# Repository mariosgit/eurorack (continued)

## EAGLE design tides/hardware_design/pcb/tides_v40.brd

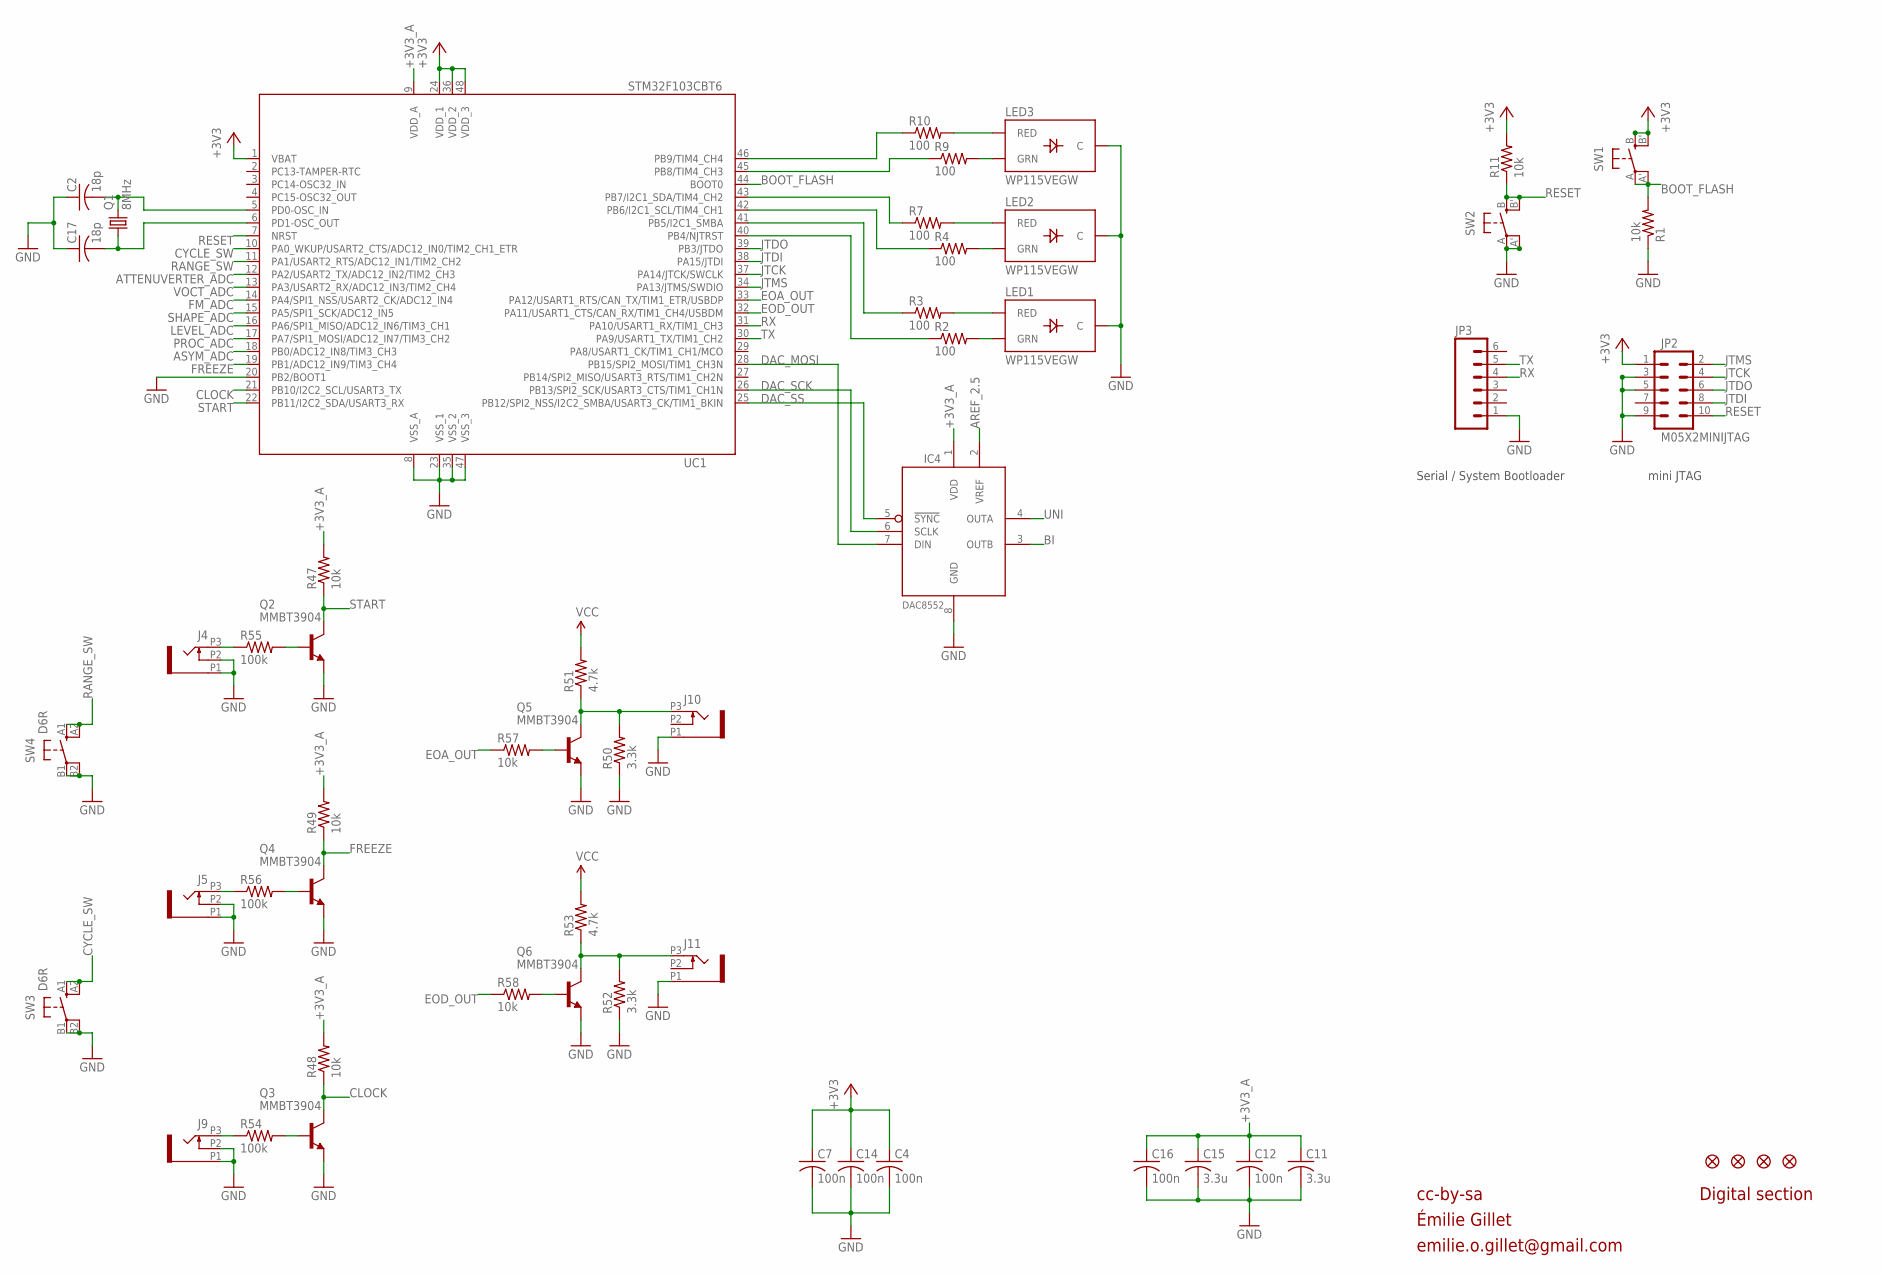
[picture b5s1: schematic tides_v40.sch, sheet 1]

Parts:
C2, C17: 18p; C0603
C4, C7, C12, C14, C16: 100n; C0603
C11, C15: 3.3u; C0603
IC4: DAC8552; MSOP-8
J4, J5, J9, J10, J11: PJ301_THONKICONN6; WQP_PJ_301M6
JP2: M05X2MINIJTAG; 2X5-1.27
JP3: M06SIP; 1X06
JP4, JP5, JP6, JP7: FIDUCIAL1X2; FIDUCIAL-1X2
LED1, LED2, LED3: WP115VEGW; LED-BICOLOR-THROUGHHOLE
Q1: 8MHz; HC49UP
Q2, Q3, Q4, Q5, Q6: MMBT3904; SOT23-BEC
R1, R11, R47, R48, R49, R57, R58: 10k; R0603
R2, R3, R4, R7, R9, R10: 100; R0603
R50, R52: 3.3k; R0603
R51, R53: 4.7k; R0603
R54, R55, R56: 100k; R0603
SW1, SW2: EVQQ2; EVQ-Q2
SW3, SW4: D6R
UC1: STM32F103CBT6; LQFP48

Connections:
+3V3: C4.1, C7.1, C14.1, JP2.1, R11.2, SW1.B (S), SW1.B' (S1), UC1.1 (VBAT), UC1.24 (VDD_1), UC1.36 (VDD_2), UC1.48 (VDD_3); also elsewhere on the board
+3V3_A: C11.1, C12.1, C15.1, C16.1, IC4.1 (VDD), R47.2, R48.2, R49.2, UC1.9 (VDD_A); also elsewhere on the board
AREF_2.5: IC4.2 (VREF); also elsewhere on the board
ASYM_ADC: UC1.18 (PB0/ADC12_IN8/TIM3_CH3); also elsewhere on the board
ATTENUVERTER_ADC: UC1.12 (PA2/USART2_TX/ADC12_IN2/TIM2_CH3); also elsewhere on the board
BI: IC4.3 (OUTB); also elsewhere on the board
BOOT_FLASH: R1.2, SW1.A, SW1.A' (P1), UC1.44 (BOOT0)
CLOCK: Q3.C, R48.1, UC1.21 (PB10/I2C2_SCL/USART3_TX)
CYCLE_SW: SW3.A1 (S), SW3.A2 (S1), UC1.10 (PA0_WKUP/USART2_CTS/ADC12_IN0/TIM2_CH1_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)
DAC_MOSI: IC4.7 (DIN), UC1.28 (PB15/SPI2_MOSI/TIM1_CH3N)
DAC_SCK: IC4.6 (SCLK), UC1.26 (PB13/SPI2_SCK/USART3_CTS/TIM1_CH1N)
DAC_SS: IC4.5 (!SYNC), UC1.25 (PB12/SPI2_NSS/I2C2_SMBA/USART3_CK/TIM1_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)
EOA_OUT: R57.1, UC1.33 (PA12/USART1_RTS/CAN_TX/TIM1_ETR/USBDP)
EOD_OUT: R58.1, UC1.32 (PA11/USART1_CTS/CAN_RX/TIM1_CH4/USBDM)
FM_ADC: UC1.14 (PA4/SPI1_NSS/USART2_CK/ADC12_IN4); also elsewhere on the board
FREEZE: Q4.C, R49.1, UC1.19 (PB1/ADC12_IN9/TIM3_CH4)
GND: C2.1, C4.2, C7.2, C11.2, C12.2, C14.2, C15.2, C16.2, C17.1, IC4.8 (GND), J4.P1 (1), J4.P2 (2), J5.P1 (1), J5.P2 (2), J9.P1 (1), J9.P2 (2), J10.P1 (1), J11.P1 (1), JP2.3, JP2.5, JP2.9, JP3.1, LED1.2 (C), LED2.2 (C), LED3.2 (C), Q2.E, Q3.E, Q4.E, Q5.E, Q6.E, R1.1, R50.1, R52.1, SW2.A, SW2.A' (P1), SW3.B1, SW3.B2 (P1), SW4.B1, SW4.B2 (P1), UC1.8 (VSS_A), UC1.20 (PB2/BOOT1), UC1.23 (VSS_1), UC1.35 (VSS_2), UC1.47 (VSS_3); also elsewhere on the board
JTCK: JP2.4, UC1.37 (PA14/JTCK/SWCLK)
JTDI: JP2.8, UC1.38 (PA15/JTDI)
JTDO: JP2.6, UC1.39 (PB3/JTDO)
JTMS: JP2.2, UC1.34 (PA13/JTMS/SWDIO)
LEVEL_ADC: UC1.16 (PA6/SPI1_MISO/ADC12_IN6/TIM3_CH1); also elsewhere on the board
unnamed: C2.2, Q1.2, UC1.5 (PD0-OSC_IN)
unnamed: C17.2, Q1.1, UC1.6 (PD1-OSC_OUT)
unnamed: J5.P3 (3), R56.1
unnamed: Q4.B, R56.2
unnamed: J9.P3 (3), R54.1
unnamed: Q3.B, R54.2
unnamed: Q6.B, R58.2
unnamed: J11.P3 (3), Q6.C, R52.2, R53.1
unnamed: LED3.3 (RED), R10.2
unnamed: LED3.1 (GRN), R9.2
unnamed: LED2.3 (RED), R7.2
unnamed: LED2.1 (GRN), R4.2
unnamed: LED1.3 (RED), R3.2
unnamed: LED1.1 (GRN), R2.2
unnamed: R10.1, UC1.46 (PB9/TIM4_CH4)
unnamed: R9.1, UC1.45 (PB8/TIM4_CH3)
unnamed: R7.1, UC1.43 (PB7/I2C1_SDA/TIM4_CH2)
unnamed: R4.1, UC1.42 (PB6/I2C1_SCL/TIM4_CH1)
unnamed: R3.1, UC1.41 (PB5/I2C1_SMBA)
unnamed: R2.1, UC1.40 (PB4/NJTRST)
unnamed: J10.P3 (3), Q5.C, R50.2, R51.1
unnamed: Q5.B, R57.2
unnamed: J4.P3 (3), R55.1
unnamed: Q2.B, R55.2
PROC_ADC: UC1.17 (PA7/SPI1_MOSI/ADC12_IN7/TIM3_CH2); also elsewhere on the board
RANGE_SW: SW4.A1 (S), SW4.A2 (S1), UC1.11 (PA1/USART2_RTS/ADC12_IN1/TIM2_CH2)
RESET: JP2.10, R11.1, SW2.B (S), SW2.B' (S1), UC1.7 (NRST)
RX: JP3.4, UC1.31 (PA10/USART1_RX/TIM1_CH3)
SHAPE_ADC: UC1.15 (PA5/SPI1_SCK/ADC12_IN5); also elsewhere on the board
START: Q2.C, R47.1, UC1.22 (PB11/I2C2_SDA/USART3_RX)
TX: JP3.5, UC1.30 (PA9/USART1_TX/TIM1_CH2)
UNI: IC4.4 (OUTA); also elsewhere on the board
VCC: R51.2, R53.2; also elsewhere on the board
VOCT_ADC: UC1.13 (PA3/USART2_RX/ADC12_IN3/TIM2_CH4); also elsewhere on the board

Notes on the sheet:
cc-by-sa
Digital section
Serial / System Bootloader
mini JTAG
Émilie Gillet
emilie.o.gillet@gmail.com

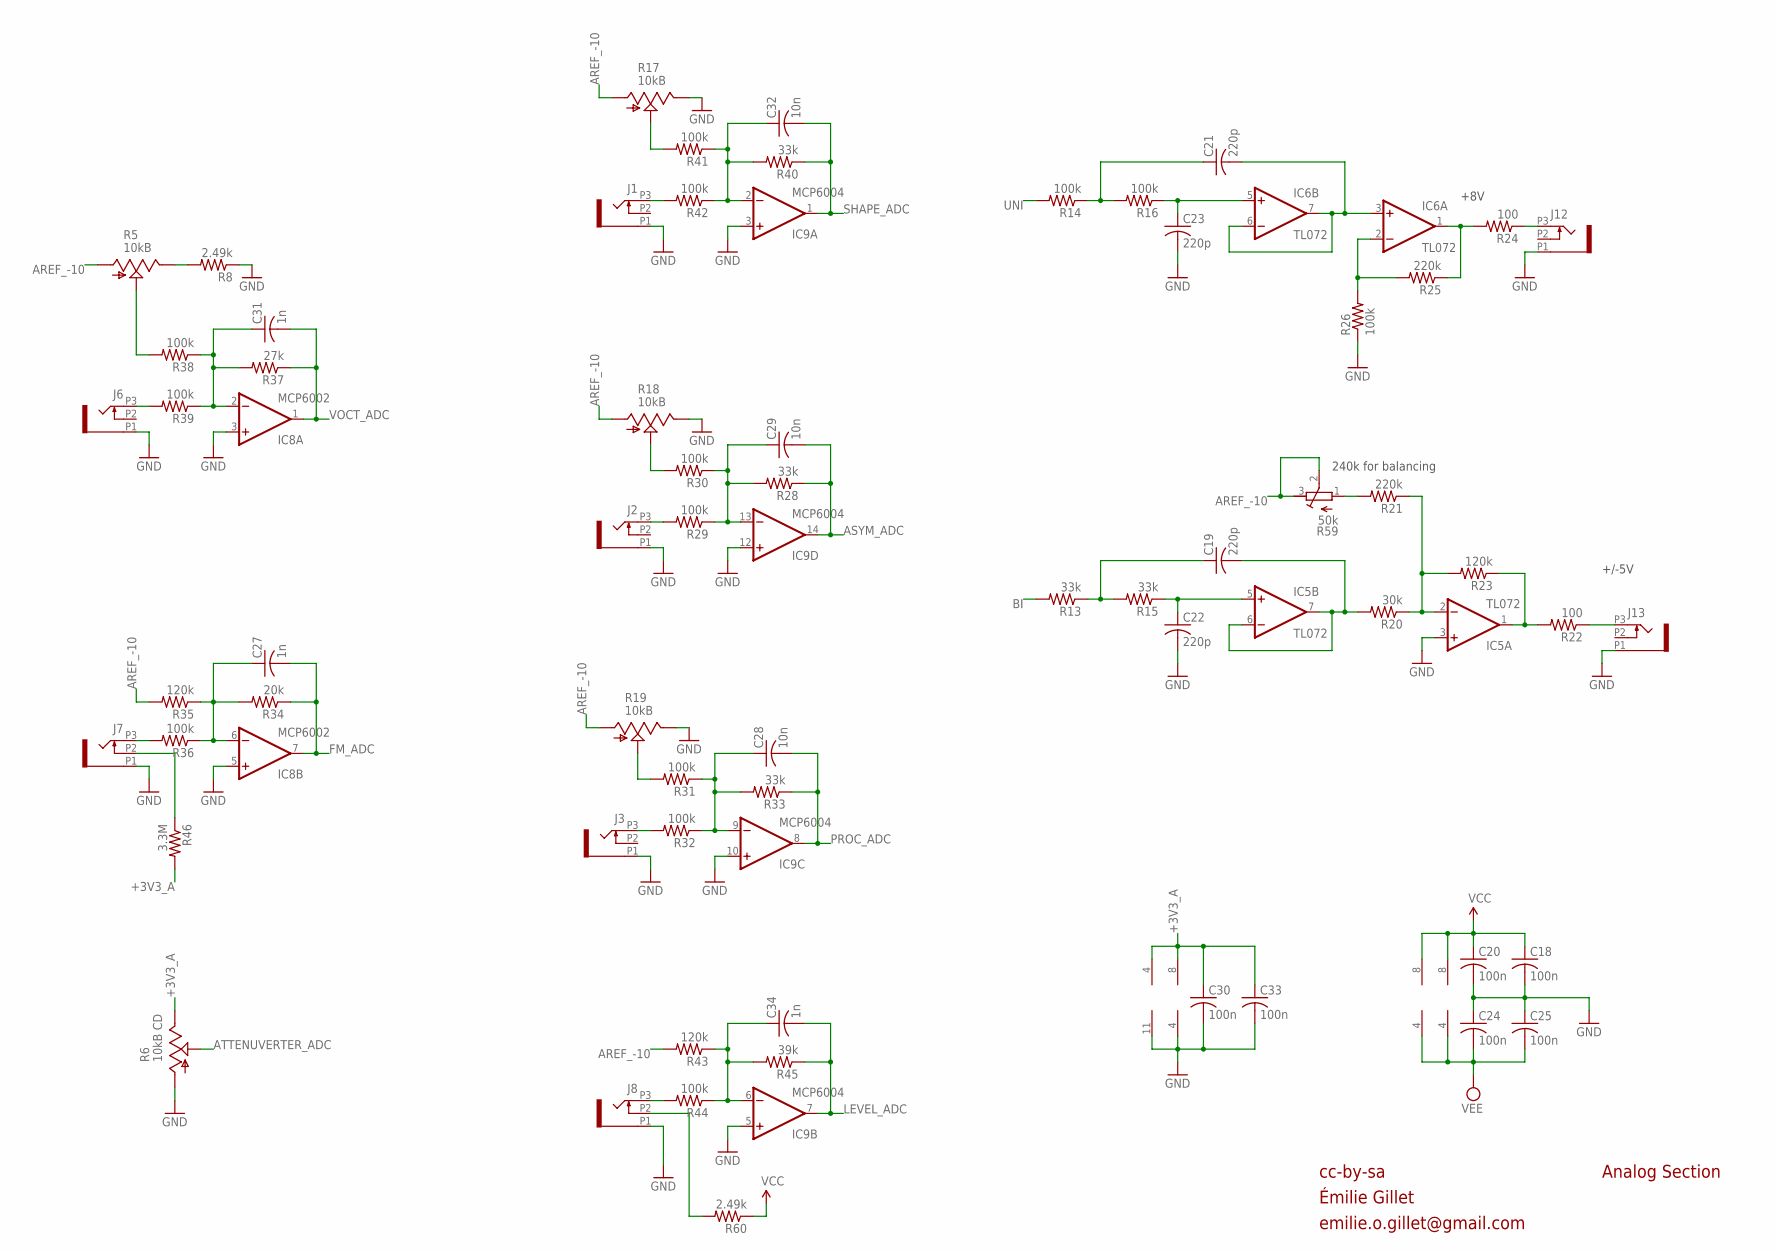
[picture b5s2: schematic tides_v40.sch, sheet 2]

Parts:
C18, C20, C24, C25, C30, C33: 100n; C0603
C19, C21, C22, C23: 220p; C0603
C27, C31, C34: 1n; C0603
C28, C29, C32: 10n; C0603
IC5, IC6: TL072; SO08
IC8: MCP6002; SO08
IC9: MCP6004; SO14
J1, J2, J3, J6, J7, J8, J12, J13: PJ301_THONKICONN6; WQP_PJ_301M6
R5, R17, R18, R19: 10kB; ALPS_POT_VERTICAL_PS
R6: 10kB CD; ALPS_POT_VERTICAL_PS
R8: 2.49k; R0603
R13, R15, R28, R33, R40: 33k; R0603
R14, R16, R26, R29, R30, R31, R32, R36, R38, R39, R41, R42, R44: 100k; R0603
R20: 30k; R0603
R21, R25: 220k; R0603
R22, R24: 100; R0603
R23, R35, R43: 120k; R0603
R34: 20k; R0603
R37: 27k; R0603
R45: 39k; R0603
R46: 3.3M; R0603
R59: 50k; RTRIM3296X
R60: 2.49k; R0805

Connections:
+3V3_A: C30.1, C33.1, IC8.8 (V+), IC9.4 (V+), R6.P$1 (E), R46.2; also elsewhere on the board
AREF_-10: R5.P$3 (A), R17.P$3 (A), R18.P$3 (A), R19.P$3 (A), R35.2, R43.2, R59.2 (S), R59.3 (A); also elsewhere on the board
ASYM_ADC: C29.2, IC9.14 (OUT), R28.1; also elsewhere on the board
ATTENUVERTER_ADC: R6.P$2 (S); also elsewhere on the board
BI: R13.2; also elsewhere on the board
BI_OUT: IC5.1 (OUT), R22.2, R23.1
FM_ADC: C27.2, IC8.7 (OUT), R34.1; also elsewhere on the board
F_CV: IC5.2 (-IN), R20.1, R21.1, R23.2
GND: C18.2, C20.2, C22.2, C23.2, C24.1, C25.1, C30.2, C33.2, IC5.3 (+IN), IC8.3 (+IN), IC8.4 (V-), IC8.5 (+IN), IC9.3 (+IN), IC9.5 (+IN), IC9.10 (+IN), IC9.11 (V-), IC9.12 (+IN), J1.P1 (1), J2.P1 (1), J3.P1 (1), J6.P1 (1), J7.P1 (1), J8.P1 (1), J12.P1 (1), J13.P1 (1), R6.P$3 (A), R8.1, R17.P$1 (E), R18.P$1 (E), R19.P$1 (E), R26.1; also elsewhere on the board
LEVEL_ADC: C34.2, IC9.7 (OUT), R45.1; also elsewhere on the board
unnamed: J1.P3 (3), R42.2
unnamed: C32.1, IC9.2 (-IN), R40.2, R41.1, R42.1
unnamed: R17.P$2 (S), R41.2
unnamed: J2.P3 (3), R29.2
unnamed: C29.1, IC9.13 (-IN), R28.2, R29.1, R30.1
unnamed: J7.P2 (2), R46.1
unnamed: R18.P$2 (S), R30.2
unnamed: J3.P3 (3), R32.2
unnamed: C28.1, IC9.9 (-IN), R31.1, R32.1, R33.2
unnamed: R19.P$2 (S), R31.2
unnamed: J8.P3 (3), R44.2
unnamed: C34.1, IC9.6 (-IN), R43.1, R44.1, R45.2
unnamed: J6.P3 (3), R39.2
unnamed: C31.1, IC8.2 (-IN), R37.2, R38.1, R39.1
unnamed: R5.P$2 (S), R38.2
unnamed: J13.P3 (3), R22.1
unnamed: R5.P$1 (E), R8.2
unnamed: J7.P3 (3), R36.2
unnamed: C27.1, IC8.6 (-IN), R34.2, R35.1, R36.1
unnamed: R21.2, R59.1 (E)
unnamed: IC6.2 (-IN), R25.2, R26.2
unnamed: C19.2, IC5.6 (-IN), IC5.7 (OUT), R20.2
unnamed: C22.1, IC5.5 (+IN), R15.1
unnamed: C19.1, R13.1, R15.2
unnamed: IC6.1 (OUT), R24.2, R25.1
unnamed: J8.P2 (2), R60.2
unnamed: C21.2, IC6.3 (+IN), IC6.6 (-IN), IC6.7 (OUT)
unnamed: C23.1, IC6.5 (+IN), R16.1
unnamed: C21.1, R14.1, R16.2
PROC_ADC: C28.2, IC9.8 (OUT), R33.1; also elsewhere on the board
SHAPE_ADC: C32.2, IC9.1 (OUT), R40.1; also elsewhere on the board
UNI: R14.2; also elsewhere on the board
UNI_OUT: J12.P3 (3), R24.1
VCC: C18.1, C20.1, IC5.8 (V+), IC6.8 (V+), R60.1; also elsewhere on the board
VEE: C24.2, C25.2, IC5.4 (V-), IC6.4 (V-); also elsewhere on the board
VOCT_ADC: C31.2, IC8.1 (OUT), R37.1; also elsewhere on the board

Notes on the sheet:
cc-by-sa
Analog Section
+8V
+/-5V
240k for balancing
Émilie Gillet
emilie.o.gillet@gmail.com

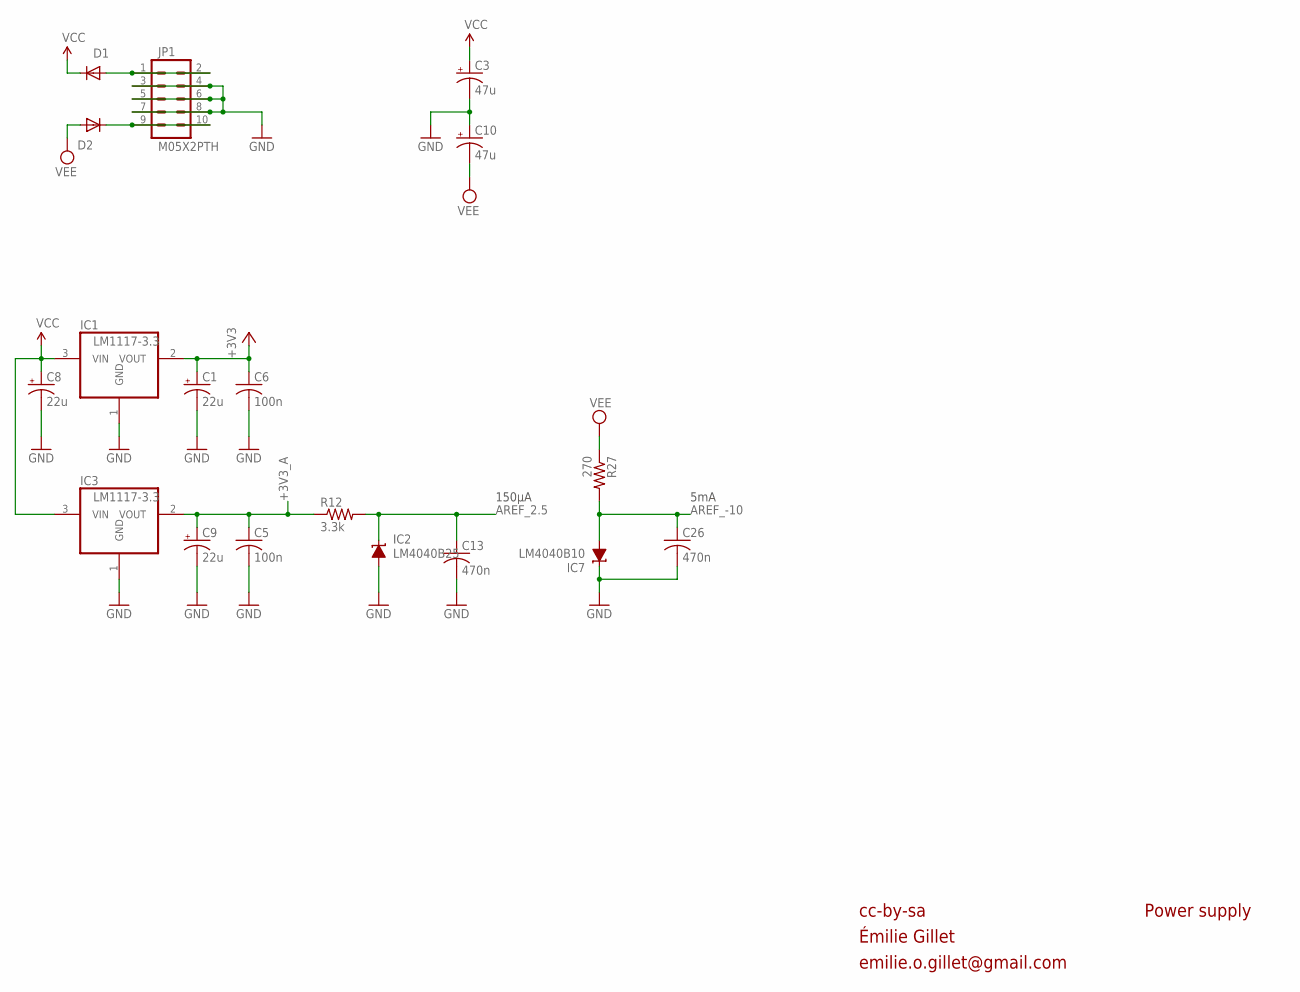
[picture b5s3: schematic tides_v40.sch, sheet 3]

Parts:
C1, C8, C9: 22u; PANASONIC_C
C3, C10: 47u; PANASONIC_D
C5, C6: 100n; C0603
C13, C26: 470n; C0603
D1, D2: 1N5819HW; SOD123
IC1, IC3: LM1117-3.3; SOT223
IC2: LM4040B25; DBZ_R-PDSO-G3
IC7: LM4040B10; DBZ_R-PDSO-G3
JP1: M05X2PTH; AVR_ICSP
R12: 3.3k; R0603
R27: 270; R0603

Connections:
+3V3: C1.+, C6.1, IC1.2 (VOUT); also elsewhere on the board
+3V3_A: C5.1, C9.+, IC3.2 (VOUT), R12.1; also elsewhere on the board
AREF_2.5: C13.1, IC2.1 (C), R12.2; also elsewhere on the board
AREF_-10: C26.1, IC7.2 (A), R27.2; also elsewhere on the board
GND: C1.-, C3.-, C5.2, C6.2, C8.-, C9.-, C10.+, C13.2, C26.2, IC1.1 (GND), IC2.2 (A), IC3.1 (GND), IC7.1 (C), JP1.3, JP1.4, JP1.5, JP1.6, JP1.7, JP1.8; also elsewhere on the board
unnamed: D1.A, JP1.1, JP1.2
unnamed: D2.C, JP1.9, JP1.10
VCC: C3.+, C8.+, D1.C, IC1.3 (VIN), IC3.3 (VIN); also elsewhere on the board
VEE: C10.-, D2.A, R27.1; also elsewhere on the board

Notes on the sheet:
cc-by-sa
Power supply
5mA
150µA
Émilie Gillet
emilie.o.gillet@gmail.com

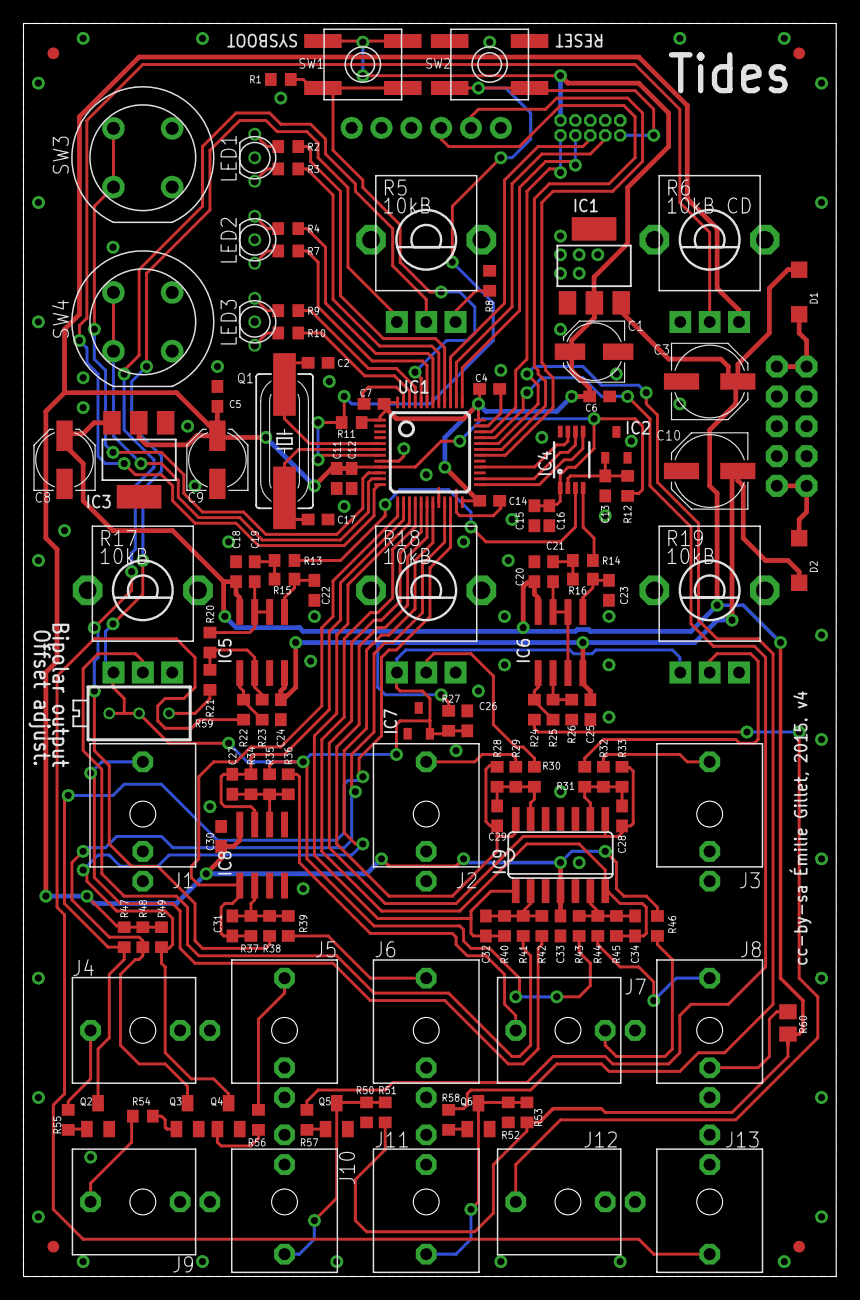
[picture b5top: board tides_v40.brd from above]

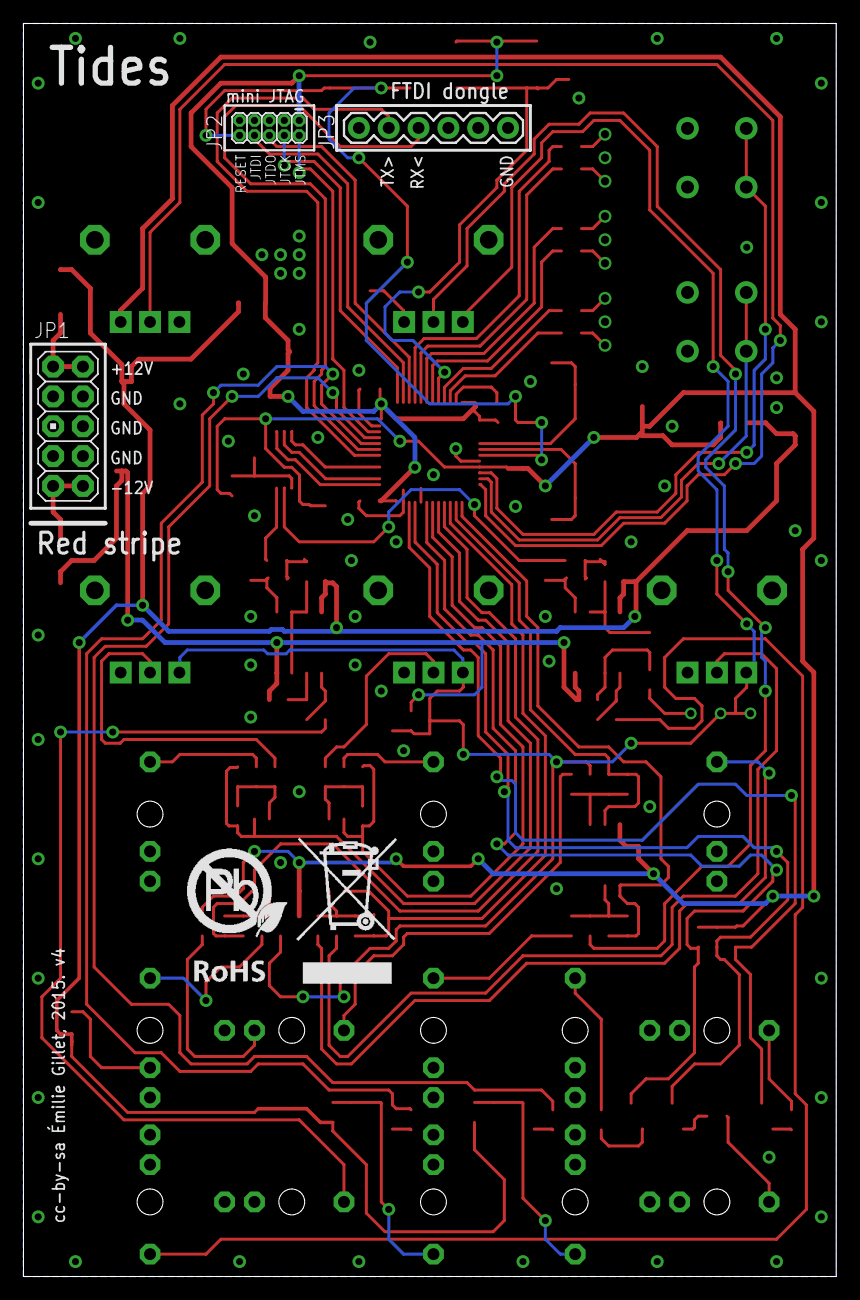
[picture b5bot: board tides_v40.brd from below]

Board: 2 copper layers, 69.2 x 106.7 mm, 140 parts (4 on the bottom side), 92 nets.

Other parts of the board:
U$3: ROHS_BIG

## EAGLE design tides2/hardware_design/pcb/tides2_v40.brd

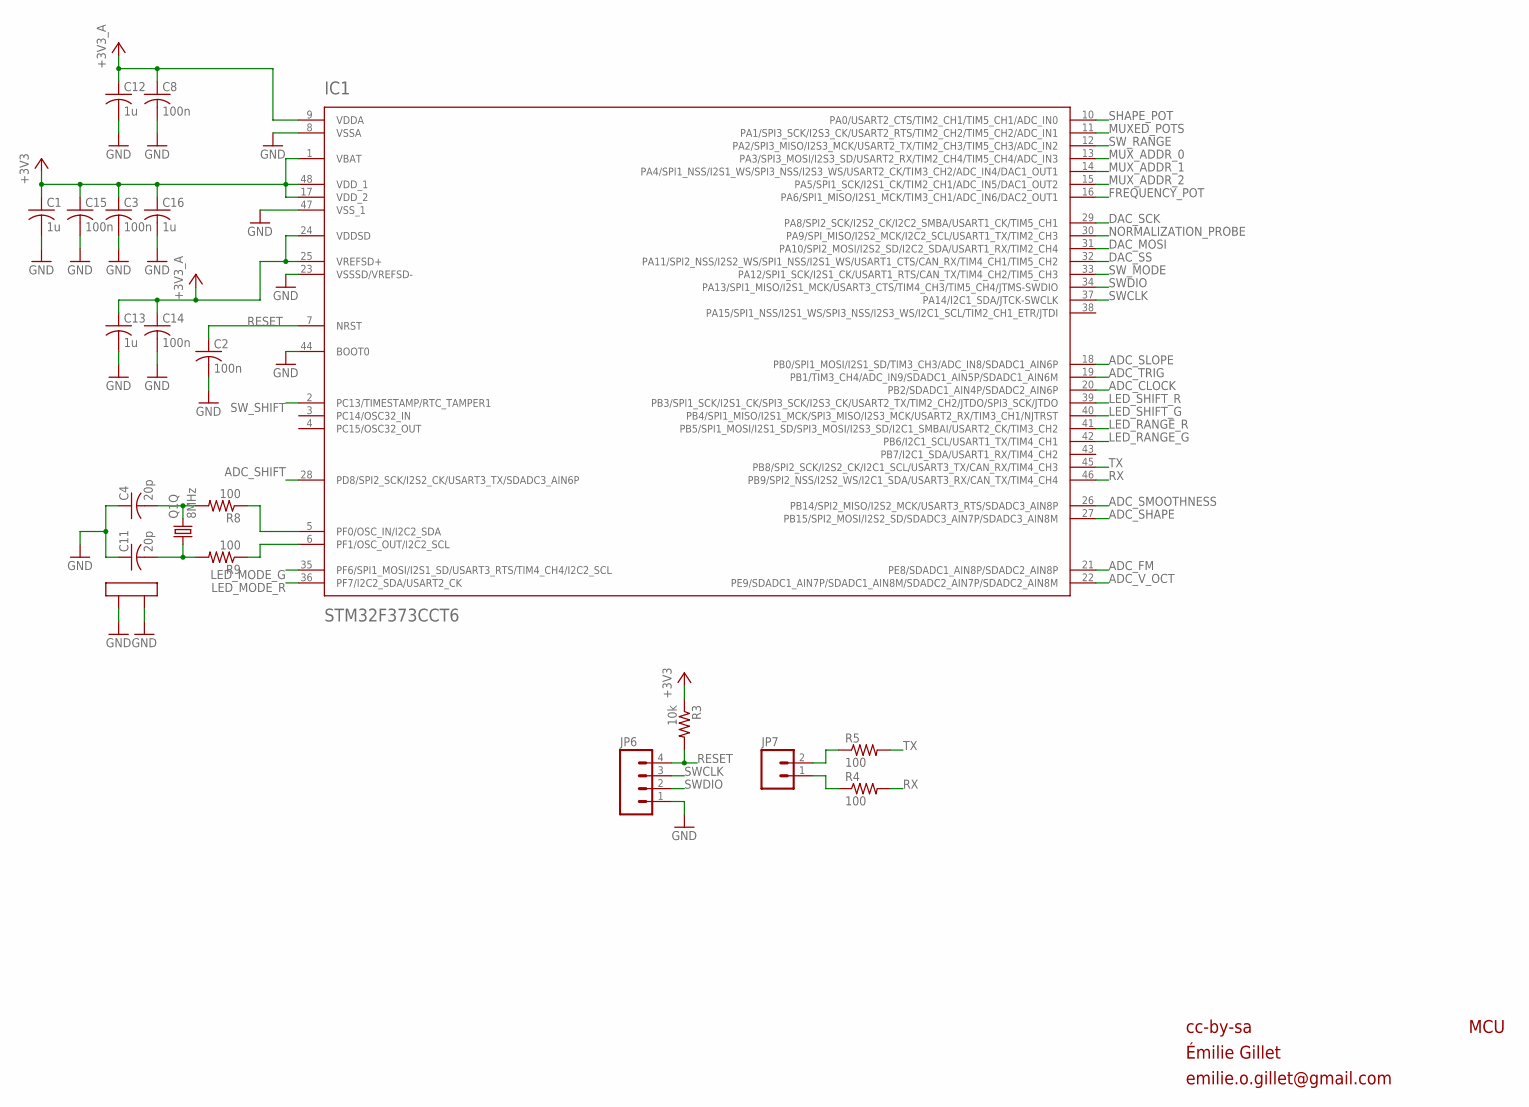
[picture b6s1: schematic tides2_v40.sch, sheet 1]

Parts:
C1, C12, C13, C16: 1u; C0402
C2, C3, C8, C14, C15: 100n; C0402
C4, C11: 20p; C0402
IC1: STM32F373CCT6; LQFP48
JP6: M04PTH; 1X04
JP7: M02PTH; 1X02
Q1: 8MHz; CTS406
R3: 10k; R0402
R4, R5, R8, R9: 100; R0402

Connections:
+3V3: C1.1, C3.1, C15.1, C16.1, IC1.1 (VBAT), IC1.17 (VDD_2), IC1.48 (VDD_1), R3.1; also elsewhere on the board
+3V3_A: C8.1, C12.1, C13.1, C14.1, IC1.9 (VDDA), IC1.24 (VDDSD), IC1.25 (VREFSD+); also elsewhere on the board
ADC_CLOCK: IC1.20 (PB2/SDADC1_AIN4P/SDADC2_AIN6P); also elsewhere on the board
ADC_FM: IC1.21 (PE8/SDADC1_AIN8P/SDADC2_AIN8P); also elsewhere on the board
ADC_SHAPE: IC1.27 (PB15/SPI2_MOSI/I2S2_SD/SDADC3_AIN7P/SDA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); also elsewhere on the board
ADC_SHIFT: IC1.28 (PD8/SPI2_SCK/I2S2_CK/USART3_TX/SDADC3_A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); also elsewhere on the board
ADC_SLOPE: IC1.18 (PB0/SPI1_MOSI/I2S1_SD/TIM3_CH3/ADC_IN8/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); also elsewhere on the board
ADC_SMOOTHNESS: IC1.26 (PB14/SPI2_MISO/I2S2_MCK/USART3_RTS/SDAD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); also elsewhere on the board
ADC_TRIG: IC1.19 (PB1/TIM3_CH4/ADC_IN9/SDADC1_AIN5P/SDADC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); also elsewhere on the board
ADC_V_OCT: IC1.22 (PE9/SDADC1_AIN7P/SDADC1_AIN8M/SDADC2_AI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); also elsewhere on the board
DAC_MOSI: IC1.31 (PA10/SPI2_MOSI/I2S2_SD/I2C2_SDA/USART1_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); also elsewhere on the board
DAC_SCK: IC1.29 (PA8/SPI2_SCK/I2S2_CK/I2C2_SMBA/USART1_C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); also elsewhere on the board
DAC_SS: IC1.32 (PA11/SPI2_NSS/I2S2_WS/SPI1_NSS/I2S1_WS/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); also elsewhere on the board
FREQUENCY_POT: IC1.16 (PA6/SPI1_MISO/I2S1_MCK/TIM3_CH1/ADC_IN6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); also elsewhere on the board
GND: C1.2, C2.2, C3.2, C4.1, C8.2, C11.1, C12.2, C13.2, C14.2, C15.2, C16.2, IC1.8 (VSSA), IC1.23 (VSSSD/VREFSD-), IC1.44 (BOOT0), IC1.47 (VSS_1), JP6.1, Q1.2 (LID1), Q1.4 (LID2); also elsewhere on the board
LED_MODE_G: IC1.35 (PF6/SPI1_MOSI/I2S1_SD/USART3_RTS/TIM4_C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); also elsewhere on the board
LED_MODE_R: IC1.36 (PF7/I2C2_SDA/USART2_CK); also elsewhere on the board
LED_RANGE_G: IC1.42 (PB6/I2C1_SCL/USART1_TX/TIM4_CH1); also elsewhere on the board
LED_RANGE_R: IC1.41 (PB5/SPI1_MOSI/I2S1_SD/SPI3_MOSI/I2S3_SD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); also elsewhere on the board
LED_SHIFT_G: IC1.40 (PB4/SPI1_MISO/I2S1_MCK/SPI3_MISO/I2S3_M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); also elsewhere on the board
LED_SHIFT_R: IC1.39 (PB3/SPI1_SCK/I2S1_CK/SPI3_SCK/I2S3_CK/U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); also elsewhere on the board
MUXED_POTS: IC1.11 (PA1/SPI3_SCK/I2S3_CK/USART2_RTS/TIM2_CH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); also elsewhere on the board
MUX_ADDR_0: IC1.13 (PA3/SPI3_MOSI/I2S3_SD/USART2_RX/TIM2_CH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); also elsewhere on the board
MUX_ADDR_1: IC1.14 (PA4/SPI1_NSS/I2S1_WS/SPI3_NSS/I2S3_WS/U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); also elsewhere on the board
MUX_ADDR_2: IC1.15 (PA5/SPI1_SCK/I2S1_CK/TIM2_CH1/ADC_IN5/D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); also elsewhere on the board
unnamed: IC1.5 (PF0/OSC_IN/I2C2_SDA), R8.1
unnamed: IC1.6 (PF1/OSC_OUT/I2C2_SCL), R9.1
unnamed: C4.2, Q1.3 (2), R8.2
unnamed: JP7.2, R5.1
unnamed: C11.2, Q1.1, R9.2
unnamed: JP7.1, R4.1
NORMALIZATION_PROBE: IC1.30 (PA9/SPI_MISO/I2S2_MCK/I2C2_SCL/USART1_T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); also elsewhere on the board
RESET: C2.1, IC1.7 (NRST), JP6.4, R3.2
RX: IC1.46 (PB9/SPI2_NSS/I2S2_WS/I2C1_SDA/USART3_RX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), R4.2
SHAPE_POT: IC1.10 (PA0/USART2_CTS/TIM2_CH1/TIM5_CH1/ADC_IN0); also elsewhere on the board
SWCLK: IC1.37 (PA14/I2C1_SDA/JTCK-SWCLK), JP6.3
SWDIO: IC1.34 (PA13/SPI1_MISO/I2S1_MCK/USART3_CTS/TIM4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), JP6.2
SW_MODE: IC1.33 (PA12/SPI1_SCK/I2S1_CK/USART1_RTS/CAN_TX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); also elsewhere on the board
SW_RANGE: IC1.12 (PA2/SPI3_MISO/I2S3_MCK/USART2_TX/TIM2_C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); also elsewhere on the board
SW_SHIFT: IC1.2 (PC13/TIMESTAMP/RTC_TAMPER1); also elsewhere on the board
TX: IC1.45 (PB8/SPI2_SCK/I2S2_CK/I2C1_SCL/USART3_TX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), R5.2

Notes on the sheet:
cc-by-sa
MCU
Émilie Gillet
emilie.o.gillet@gmail.com

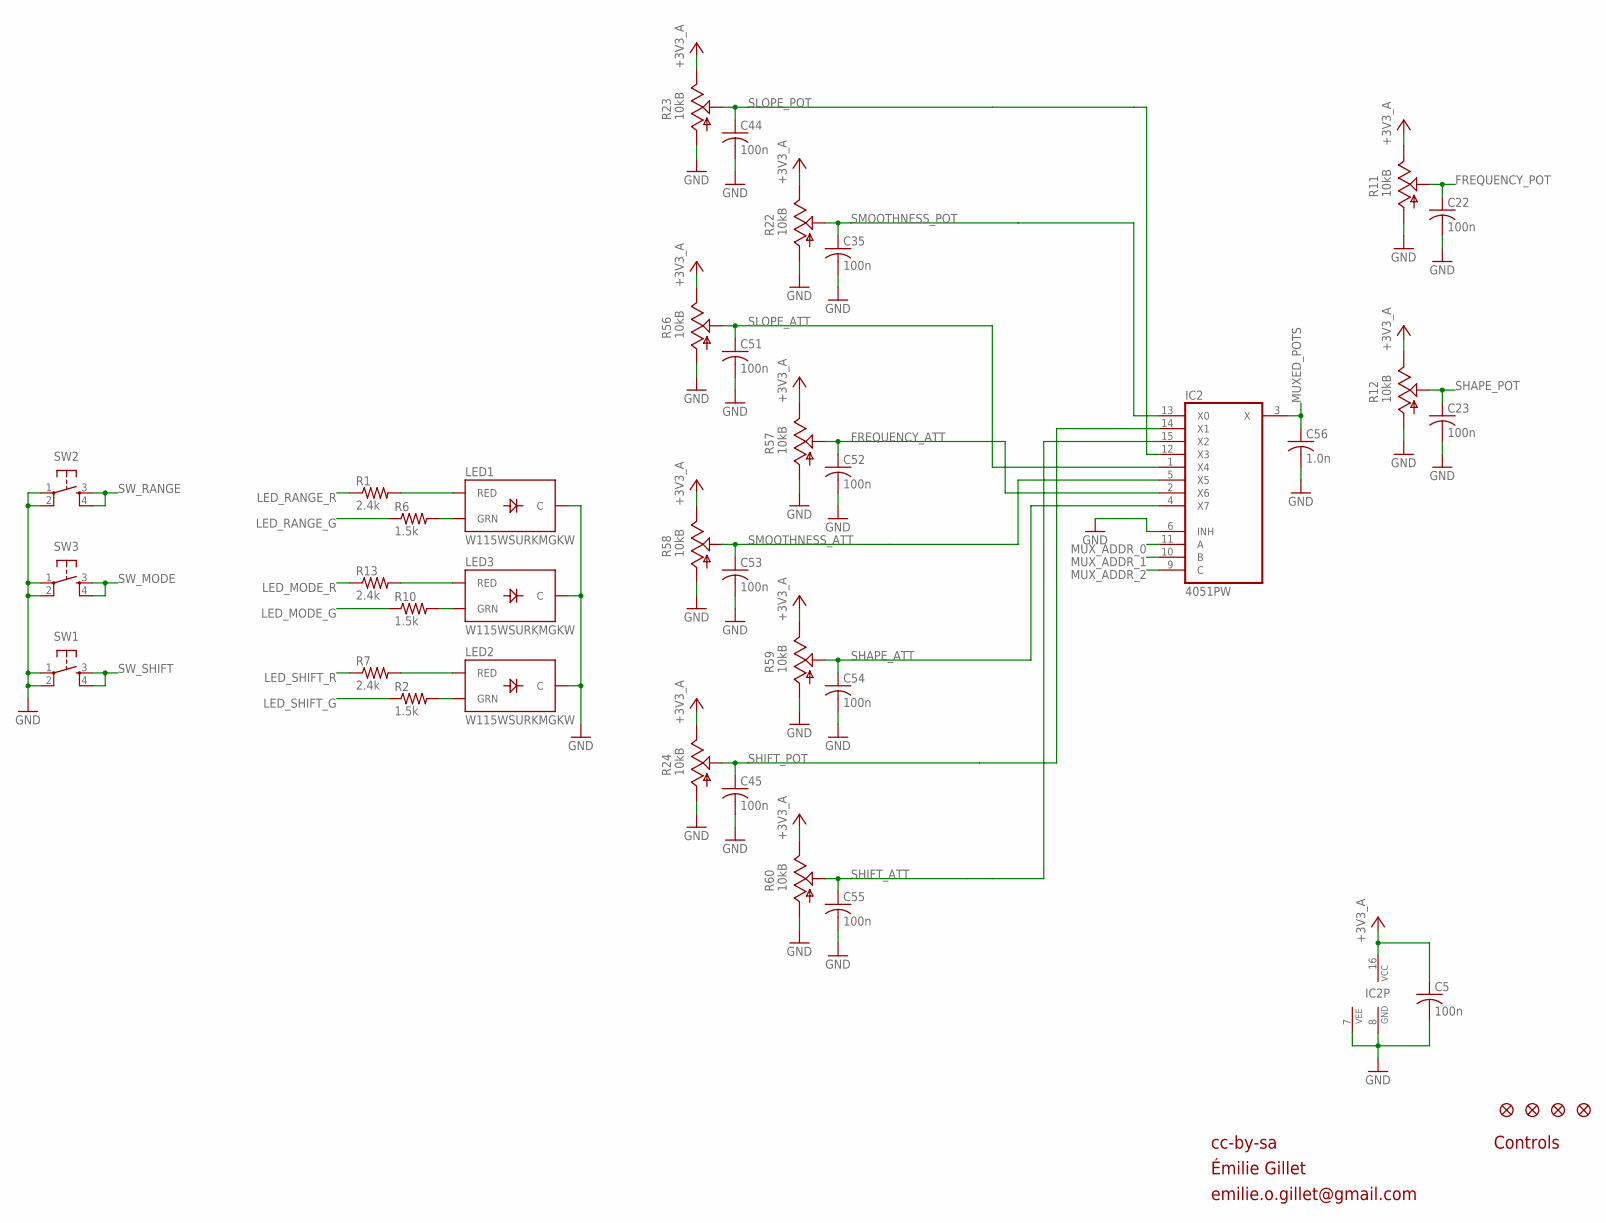
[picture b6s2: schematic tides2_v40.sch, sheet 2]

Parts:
C5, C22, C23, C35, C44, C45, C51, C52, C53, C54, C55: 100n; C0402
C56: 1.0n; C0402
IC2: 4051PW; TSSOP16_065
JP1, JP2, JP3, JP4: FIDUCIAL1X2; FIDUCIAL-1X2
LED1, LED2, LED3: W115WSURKMGKW; LED-BICOLOR-THROUGHHOLE-2.54
R1, R7, R13: 2.4k; R0402
R2, R6, R10: 1.5k; R0402
R11, R12, R22, R23, R24: 10kB; ALPS_POT_VERTICAL_PS
R56, R57, R58, R59, R60: 10kB; ALPS_POT_VERTICAL
SW1, SW2, SW3: TAC_SWITCHPTH; TACTILE-PTH

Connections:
+3V3_A: C5.1, IC2.16 (VCC), R11.P$1 (E), R12.P$1 (E), R22.P$1 (E), R23.P$1 (E), R24.P$1 (E), R56.P$1 (E), R57.P$1 (E), R58.P$1 (E), R59.P$1 (E), R60.P$1 (E); also elsewhere on the board
FREQUENCY_ATT: C52.1, IC2.2 (X6), R57.P$2 (S)
FREQUENCY_POT: C22.1, R11.P$2 (S); also elsewhere on the board
GND: C5.2, C22.2, C23.2, C35.2, C44.2, C45.2, C51.2, C52.2, C53.2, C54.2, C55.2, C56.2, IC2.6 (INH), IC2.7 (VEE), IC2.8 (GND), LED1.2 (C), LED2.2 (C), LED3.2 (C), R11.P$3 (A), R12.P$3 (A), R22.P$3 (A), R23.P$3 (A), R24.P$3 (A), R56.P$3 (A), R57.P$3 (A), R58.P$3 (A), R59.P$3 (A), R60.P$3 (A), SW1.1, SW1.2, SW2.1, SW2.2, SW3.1, SW3.2; also elsewhere on the board
LED_MODE_G: R10.1; also elsewhere on the board
LED_MODE_R: R13.1; also elsewhere on the board
LED_RANGE_G: R6.1; also elsewhere on the board
LED_RANGE_R: R1.1; also elsewhere on the board
LED_SHIFT_G: R2.1; also elsewhere on the board
LED_SHIFT_R: R7.1; also elsewhere on the board
MUXED_POTS: C56.1, IC2.3 (X); also elsewhere on the board
MUX_ADDR_0: IC2.11 (A); also elsewhere on the board
MUX_ADDR_1: IC2.10 (B); also elsewhere on the board
MUX_ADDR_2: IC2.9 (C); also elsewhere on the board
unnamed: LED1.3 (RED), R1.2
unnamed: LED3.3 (RED), R13.2
unnamed: LED3.1 (GRN), R10.2
unnamed: LED2.3 (RED), R7.2
unnamed: LED1.1 (GRN), R6.2
unnamed: LED2.1 (GRN), R2.2
SHAPE_ATT: C54.1, IC2.4 (X7), R59.P$2 (S)
SHAPE_POT: C23.1, R12.P$2 (S); also elsewhere on the board
SHIFT_ATT: C55.1, IC2.15 (X2), R60.P$2 (S)
SHIFT_POT: C45.1, IC2.14 (X1), R24.P$2 (S)
SLOPE_ATT: C51.1, IC2.1 (X4), R56.P$2 (S)
SLOPE_POT: C44.1, IC2.12 (X3), R23.P$2 (S)
SMOOTHNESS_ATT: C53.1, IC2.5 (X5), R58.P$2 (S)
SMOOTHNESS_POT: C35.1, IC2.13 (X0), R22.P$2 (S)
SW_MODE: SW3.3, SW3.4; also elsewhere on the board
SW_RANGE: SW2.3, SW2.4; also elsewhere on the board
SW_SHIFT: SW1.3, SW1.4; also elsewhere on the board

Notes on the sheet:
cc-by-sa
Controls
Émilie Gillet
emilie.o.gillet@gmail.com
